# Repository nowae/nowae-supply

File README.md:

# nowae-supply

Created with KiCad 5.99

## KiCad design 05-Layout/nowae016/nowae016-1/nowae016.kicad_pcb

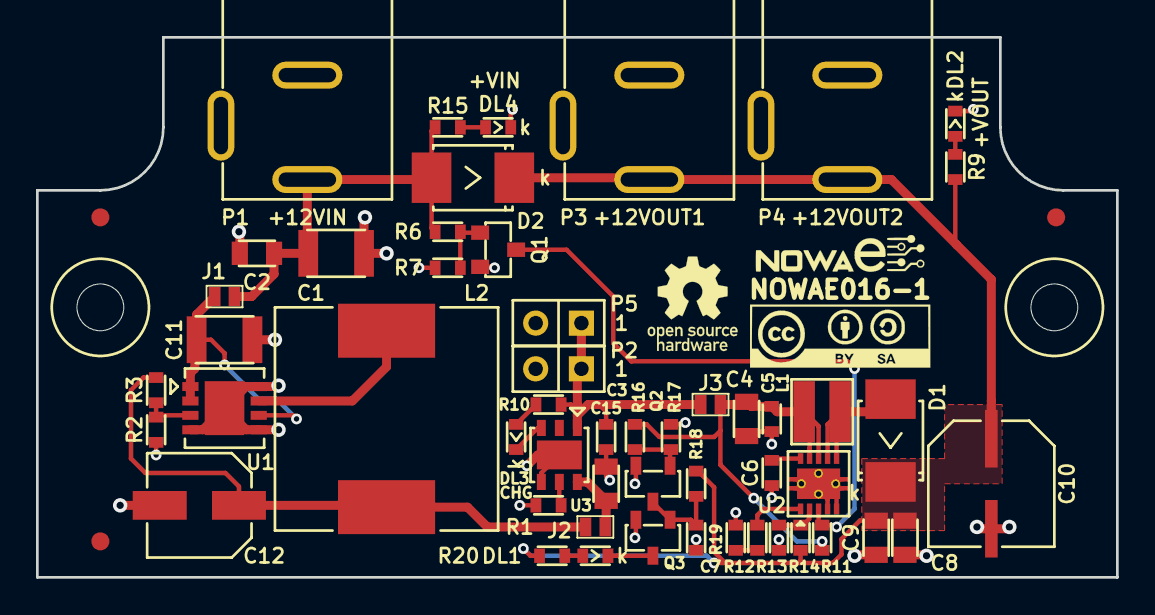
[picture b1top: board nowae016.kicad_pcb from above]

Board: 2 copper layers, 60.0 x 30.0 mm, 55 parts (0 on the bottom side), 26 nets.

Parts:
C1: 22u; CAPACITOR-1210
C2: 100n; CAPACITOR-0805
C3: 2u2; CAPACITOR-0603
C4: 22u; CAPACITOR-0805
C5: 1u; CAPACITOR-0603
C6: 100n; CAPACITOR-0603
C7: 820p; CAPACITOR-0603
C8, C9: 10u; CAPACITOR-0805
C10: 47u; CAPACITOR-6.3x5.3
C11: 10u; CAPACITOR-1210
C12: 47u; CAPACITOR-5.0x5.5
C15: 47u; CAPACITOR-0805
D1, D2: SS22; DIODE-DO214AA-UNI
DL1: RED; LED-0603
DL2, DL3: YELLOW; LED-0603
DL4: GREEN; LED-0603
J1, J2, J3: JUMPER-2; JUMPERSMD-2
L1: 3u3; INDUCTOR_WE-MAPI-3020
L2: 8u2; INDUCTOR_WE-PD-1260
P1, P3, P4: BARRELJACK; BARRELJACK-WE-694106301002
P2, P5: CONN_2X1; CONN-STRIP-2x1-2.54
Q1, Q2, Q3: BCW66GLT; SOT23-3
R1: 3k9; RESISTOR-0603
R2: 2k1; RESISTOR-0603
R3: 11k; RESISTOR-0603
R6, R18: 140k; RESISTOR-0603
R7, R19: 10k; RESISTOR-0603
R9, R10, R12, R13, R15, R20: 18k; RESISTOR-0603
R11, R17: 100k; RESISTOR-0603
R14: 154k; RESISTOR-0603
R16: 360k; RESISTOR-0603
U1: ST1S10PUR; DFN8_4.0x4.0_0.8
U2: TPS61087DRCR; WSON10_3.0x3.0_0.5_10+1
U3: STBC08PMR; DFN6_3.0x3.0_1.0
VAL**: FIDUCIAL-TOP
VAL**#2, VAL**#3: FIDUCIAL-TOP

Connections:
+12V: C8.1, C9.1, C10.1, D1.2, D2.2, P3.1, P4.1, R9.2, R14.1, R18.2, R20.1
+VBAT: C3.1, J3.1, P2.1, P5.1, R10.2, U3.1
+VIN: C1.1, C2.1, D2.1, J1.1, P1.1, R6.1, R15.1
/0V8: Q1.1, R6.2, R7.1
/~CHG: DL3.2, U3.3
GND: C1.2, C2.2, C3.2, C4.2, C5.2, C6.2, C7.2, C8.2, C9.2, C10.2, C11.2, C12.2, C15.2, DL2.2, DL4.2, P1.2, P1.3, P2.2, P3.2, P3.3, P4.2, P4.3, P5.2, Q1.2, Q2.2, Q3.2, R1.2, R2.2, R7.2, R13.2, R17.1, R19.1, U1.4, U1.5, U1.8, U1.9, U2.4, U2.5, U2.11, U3.4, U3.7
unnamed: C4.1, C5.1, J3.2, L1.1, R11.1, R16.2, U2.8, U2.9
unnamed: C6.1, U2.10
unnamed: C7.1, R12.2
unnamed: C11.1, J1.2, U1.1, U1.2, U1.6
unnamed: C12.1, J2.1, L2.2, R3.2
unnamed: C15.1, J2.2, U3.6
unnamed: D1.1, L1.2, U2.6, U2.7
unnamed: DL1.1, R20.2
unnamed: DL1.2, Q3.3
unnamed: DL2.1, R9.1
unnamed: DL3.1, R10.1
unnamed: DL4.1, R15.2
unnamed: L2.1, U1.7
unnamed: Q1.3, R11.2, U2.3
unnamed: Q2.1, R16.1, R17.2
unnamed: Q2.3, Q3.1, R18.1, R19.2
unnamed: R1.1, U3.5
unnamed: R2.1, R3.1, U1.3
unnamed: R12.1, U2.1
unnamed: R13.1, R14.2, U2.2

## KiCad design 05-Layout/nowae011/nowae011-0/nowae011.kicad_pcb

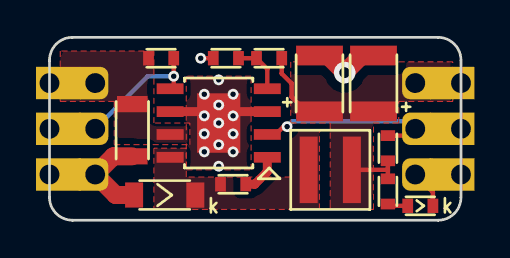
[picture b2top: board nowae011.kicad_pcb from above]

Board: 2 copper layers, 22.9 x 10.2 mm, 15 parts (0 on the bottom side), 9 nets.

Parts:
C1, C4: 10u; CAPACITOR-1210
C2: 4u7; CAPACITOR-1206
C3: 100n; CAPACITOR-0603
D1: SS36FA; DIODE-SOD123
DL1: GREEN; LED-0603
L1: 8u5; INDUCTOR-WURTH-4030
P1: VIN; CONN-HALFHOLE-3x1-2.54
P2: VOUT; CONN-HALFHOLE-3x1-2.54
R1: 2k7; RESISTOR-0603
R2, R5: 100k; RESISTOR-0603
R3: 8k45; RESISTOR-0603
R4: 220; RESISTOR-0603
U1: ST1S14PHR; HSOIC8_3.9x4.9_1.27

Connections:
+5V: C1.1, C4.1, L1.2, P2.3, R2.1, R3.1, R4.2
+24V: C2.1, P1.1, R5.2, U1.7
/EN2: P1.2, R5.1, U1.5
/~PG: P2.2, R2.2, U1.2
GND: C1.2, C2.2, C4.2, D1.1, DL1.2, P1.3, P2.1, R1.2, U1.3, U1.6, U1.9
unnamed: C3.1, U1.1
unnamed: C3.2, D1.2, L1.1, U1.8
unnamed: DL1.1, R4.1
unnamed: R1.1, R3.2, U1.4

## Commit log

2018-10-24 Added project nowae011-0 (nowae011-0)
2018-10-24 Added schematic (nowae011-0)
2018-10-24 Added informations about inductor (nowae011-0)
2018-10-24 Changed partition divider (nowae011-0)
2018-10-24 Changed led resistor and led informations (nowae011-0)
2018-10-26 Added project structure (nowae011-0)
2018-10-29 Added components informations and associated footprint (nowae011-0)
2018-10-29 Updated fp-lib-table (nowae011-0)
2018-10-29 Annotated components (nowae011-0)
2018-10-29 Added netlist (nowae011-0) Added pcb (nowae011-0)
2018-10-29 Updated pcb (nowae011-0)
2018-10-29 WiP: placement silkscreen (nowae011-0)
2018-10-29 Fixed pcb (nowae011-0)
2018-10-30 Updated schematic (nowae011-0)
2018-10-30 Updated netlist (nowae011-0) WiP: placement components (nowae011-0)
2018-11-06 Updated schematic, netfile (nowae011-0) WiP: placement components (nowae011-0)
2018-11-06 WiP: placement wires (nowae011-0)
2018-11-07 Fixed silkscreen top (nowae011-0)
2019-02-01 Added project structure (nowae016-0)
2019-02-02 Added schematic (nowae016-0)
2019-02-02 Added sym-lib-table (nowae016-0)
2019-02-03 Changed battery charger (nowae016-0)
2019-02-03 Changed I/O connectors (nowae016-0)
2019-02-03 Associated footprints (nowae016-0)
2019-02-23 Changed led and added output connector (nowae016-0)
2019-02-23 Minor fix (nowae016-0)
2019-02-23 Fixed footprint association (nowae016-0)
2019-02-24 Added P2 connector (nowae016-0)
2019-02-25 Added datasheets (nowae016-0)
2019-02-26 Updated BOM table (nowae016-0)
2019-03-28 Updated BOM (nowae016-0)
2019-03-28 Added pcb (nowae016-0)
2019-03-28 Added net file (nowae016-0)
2019-03-29 WiP: layout (nowae016-0)
2019-03-29 WiP: schematic (nowae016-0)
2019-08-25 Fixed schematic (nowae011-0)
2019-08-25 Added datasheets into 04-Documents/01-Datasheet (nowae011-0)
2019-08-25 Added gerber files into 07-Production/02-Gerber (nowae011-0)
2019-08-25 Added 3D photo into 07-Production/04-Photos (nowae011-0)
2019-08-31 Added BOM into 07-Production/03-BOM/nowae011 (nowae011-0)
2019-08-31 Updated worksheet (nowae011-0)
2019-08-31 Added assembly files into 07-Production/04-Assembly/nowae011 (nowae011-0)
2019-08-31 Updated nowae011.pro (nowae011-0)
2020-10-17 Added first revision (nowae016-1)
2020-10-17 Added gerber (nowae016-1)
2020-10-19 Fix silkscreen (nowae016-1)
2020-10-19 Added gerber file (nowae016-1)
2021-04-05 Added simulation DimmingInterface.asc into 02-Drafts
2021-04-05 Created README.md
2021-04-05 Added documents
2021-04-05 Moved DimmingInterface.asc into 03-Simulations
2021-04-05 Added project (NOWAE031-0)
2021-04-05 WiP: schematic (NOWAE031-0)
